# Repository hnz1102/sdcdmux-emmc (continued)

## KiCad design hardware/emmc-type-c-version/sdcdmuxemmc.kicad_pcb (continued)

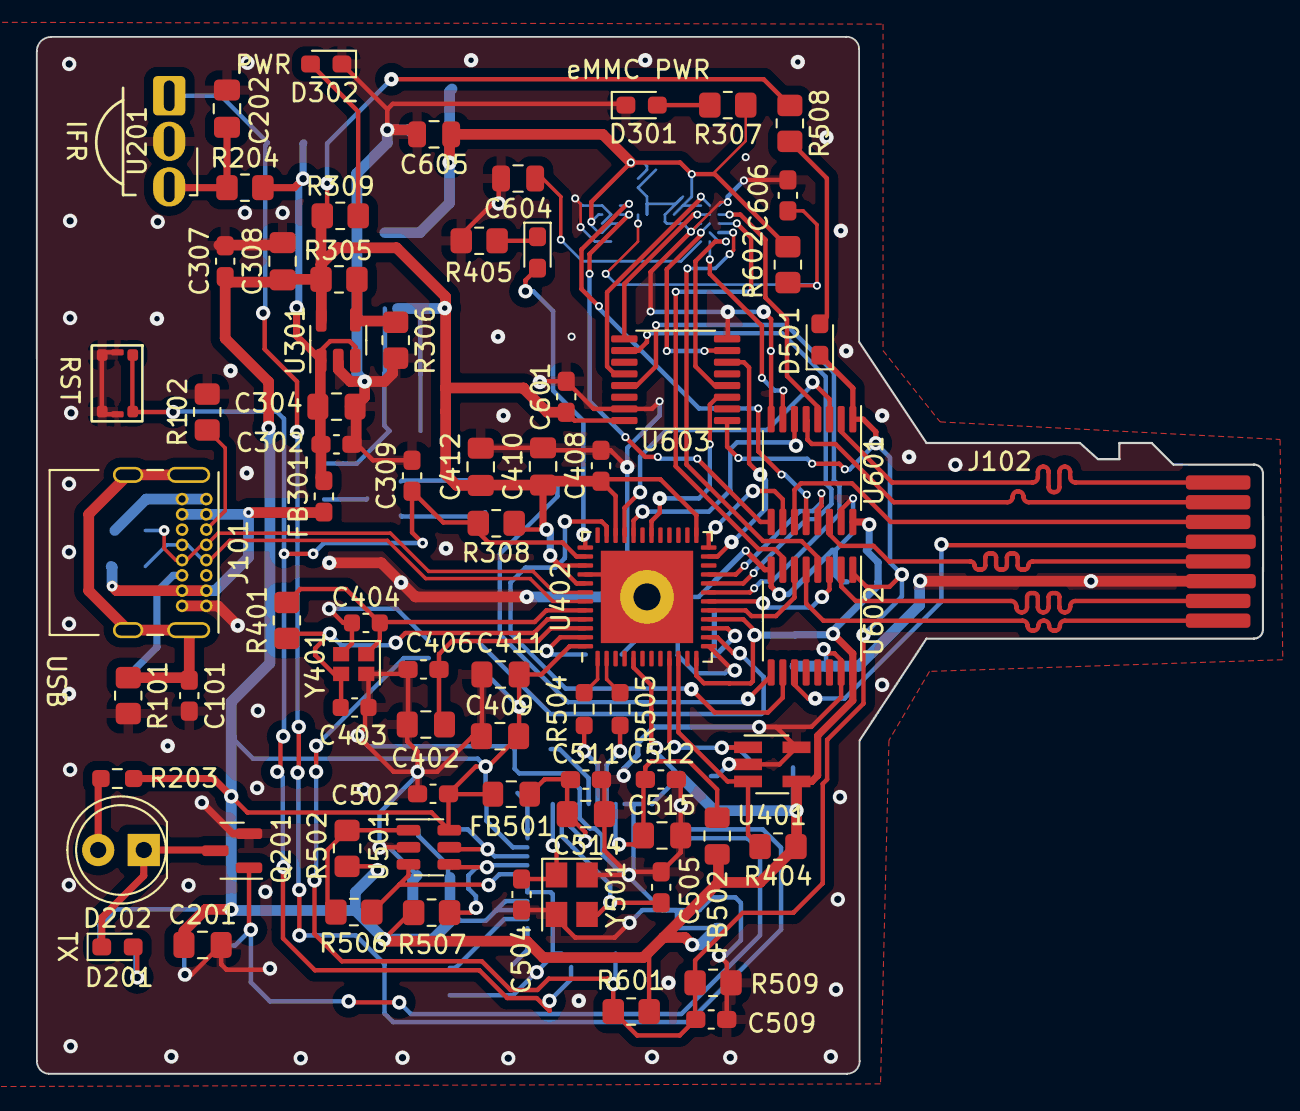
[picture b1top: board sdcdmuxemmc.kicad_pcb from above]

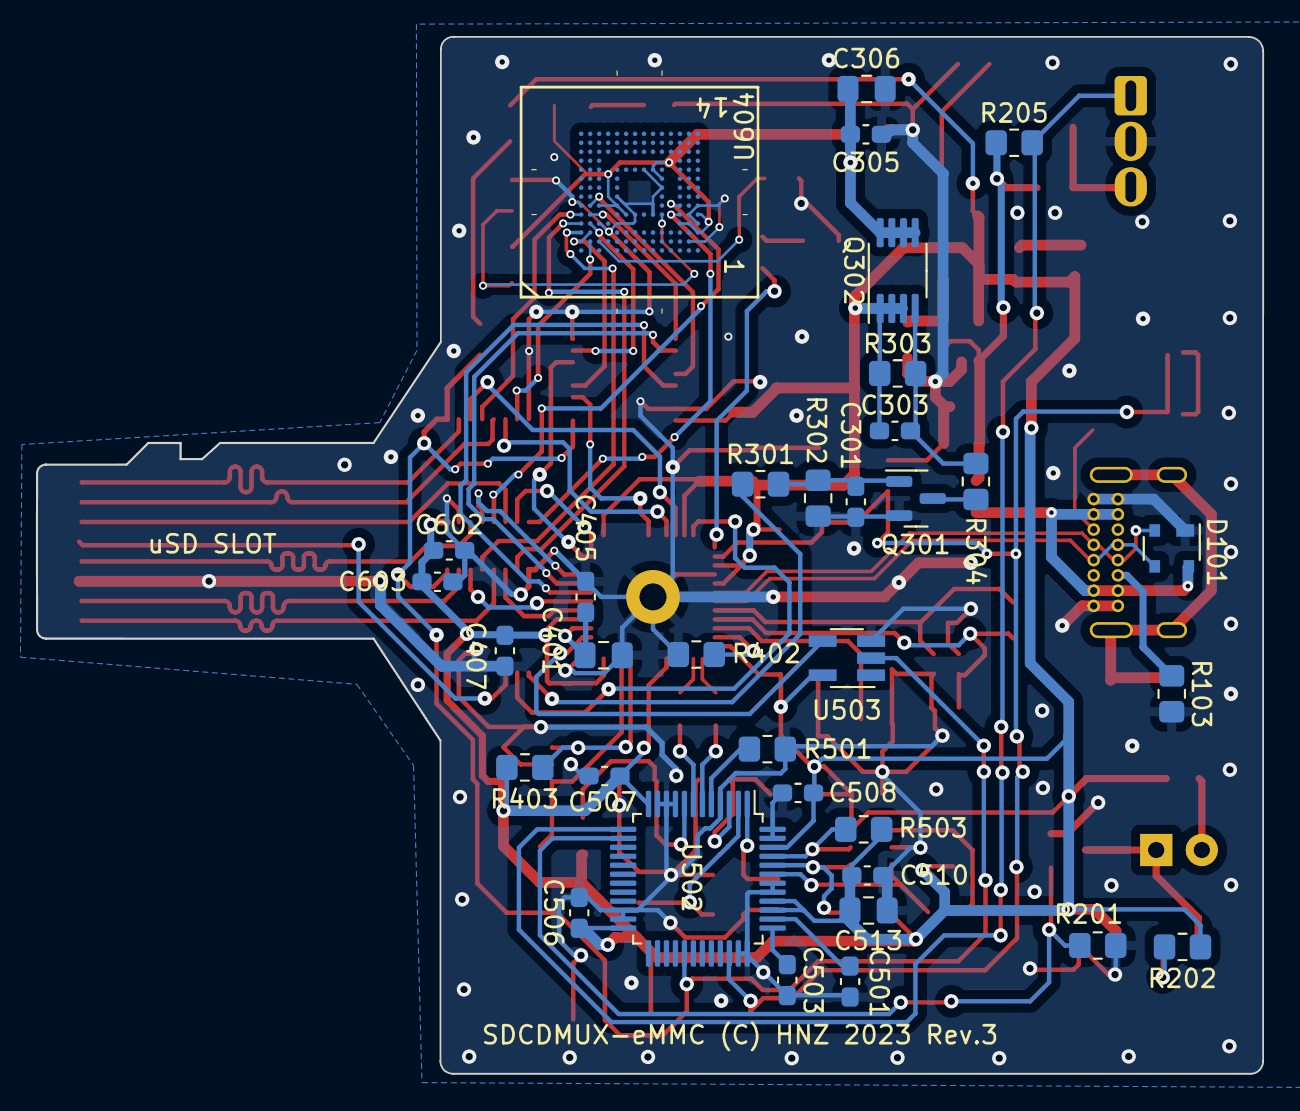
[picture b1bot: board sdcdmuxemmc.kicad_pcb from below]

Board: 2 copper layers, 68.3 x 57.8 mm, 107 parts (34 on the bottom side), 81 nets.

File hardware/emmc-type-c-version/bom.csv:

"Reference","Value","Footprint","digikey","storeURL","Qty"
"C101, C301, C302, C305, C307, C309, C405-C408, C501-C503, C506-C512, C601-C603, C606","0.1uF","Capacitor_SMD:C_0603_1608Metric_Pad1.08x0.95mm_HandSolder","311-1824-1-ND","https://www.digikey.com/en/products/detail/yageo/CC0603MRX7R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","24"
"C201, C304, C306, C308","10uF","Capacitor_SMD:C_0805_2012Metric_Pad1.18x1.45mm_HandSolder","311-3494-1-ND","https://www.digikey.com/en/products/detail/yageo/CC0603MRX5R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","4"
"C202","22uF","Capacitor_SMD:C_0805_2012Metric_Pad1.18x1.45mm_HandSolder","311-3494-1-ND","https://www.digikey.com/en/products/detail/yageo/CC0603MRX5R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","1"
"C303","2.2uF","Capacitor_SMD:C_0603_1608Metric_Pad1.08x0.95mm_HandSolder","311-1795-1-ND","https://www.digikey.com/en/products/detail/yageo/CC0603KRX7R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","1"
"C401, C402, C409, C410","1uF","tbctl:C_0805_2012Metric_Pad1.18x1.45mm_HandSolder","13-CC0603KPX7R7BB105CT-ND","https://www.digikey.com/en/products/detail/yageo/CC0603KPX7R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","4"
"C403, C404","27pF","Capacitor_SMD:C_0603_1608Metric","311-1063-1-ND","https://www.digikey.com/en/products/detail/yageo/CC0603JRNPO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","2"
"C411, C412","4.7uF","tbctl:C_0805_2012Metric_Pad1.18x1.45mm_HandSolder","311-1455-1-ND","https://www.digikey.com/en/products/detail/yageo/CC0603KRX5R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","2"
"C504, C505","27pF","Capacitor_SMD:C_0603_1608Metric_Pad1.08x0.95mm_HandSolder","311-1063-1-ND","https://www.digikey.com/en/products/detail/yageo/CC0603JRNPO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","2"
"C513-C515","4.7uF","Capacitor_SMD:C_0805_2012Metric_Pad1.18x1.45mm_HandSolder","311-1455-1-ND","https://www.digikey.com/en/products/detail/yageo/CC0603KRX5R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","3"
"C604, C605","1uF","Capacitor_SMD:C_0805_2012Metric","13-CC0603KPX7R7BB105CT-ND","https://www.digikey.com/en/products/detail/yageo/CC0603KPX7R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","2"
"D101","PRTR5V0U2X","Package_TO_SOT_SMD:SOT-143","1727-3884-1-ND","https://www.digikey.com/en/products/detail/nexperia-usa-inc/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","1"
"D201, D302, D401","LED RED","tbctl:LED_0603_1608Metric_Pad1.05x0.95mm_HandSolder","511-1587-1-ND","https://www.digikey.com/en/products/detail/rohm-semiconducto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","3"
"D202","OED-EL-1L2","LED_THT:LED_D5.0mm","67-1001-ND","https://www.digikey.com/en/products/detail/lumex-opto-compon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","1"
"D301","eMMC PWR LED RED","tbctl:LED_0603_1608Metric_Pad1.05x0.95mm_HandSolder","511-1587-1-ND","https://www.digikey.com/en/products/detail/rohm-semiconducto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","1"
"D501","TGT SEL LED BLUE","tbctl:LED_0603_1608Metric_Pad1.05x0.95mm_HandSolder","846-1177-1-ND","https://www.digikey.com/en/products/detail/rohm-semiconducto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","1"
"FB301","BK2125HS601-T","tbctl:L_0603_1608Metric_Pad1.05x0.95mm_HandSolder","240-2399-1-ND ","https://www.digikey.com/en/products/detail/laird-signal-inte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","1"
"FB501, FB502","BK2125HS601-T","Inductor_SMD:L_0805_2012Metric_Pad1.15x1.40mm_HandSolder","240-2399-1-ND ","https://www.digikey.com/en/products/detail/laird-signal-inte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","2"
"J101","USB_C_Receptacle_USB2.0_GCT4085","Connector_USB:USB_C_Receptacle_GCT_USB4085","2073-USB4085-GF-ACT-ND","https://www.digikey.com/en/products/detail/gct/USB4085-GF-A/9859662","1"
"J102","uSD-CARD-PAD","tbctl:uSD Card Pad","","","1"
"Q201, Q301","2N7002K","Package_TO_SOT_SMD:SOT-23","2N7002K-7DICT-ND","https://www.digikey.com/en/products/detail/diodes-incorporat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","2"
"Q302","IRF7606TRPBF","Package_SO:MSOP-8_3x3mm_P0.65mm","IRF7606TRPBFCT-ND","https://www.digikey.com/en/products/detail/infineon-technolo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","1"
"R101, R201, R205, R302, R303, R308, R403, R404, R502, R503, R507, R509, R601, R602","10K","tbctl:R_0805_2012Metric_Pad1.20x1.40mm_HandSolder","13-RC0603JR-1010KLCT-ND","https://www.digikey.com/en/products/detail/yageo/RC0603JR-10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","14"
"R102, R103","5.1K","tbctl:R_0805_2012Metric_Pad1.20x1.40mm_HandSolder","13-RC0603JR-1010KLCT-ND","https://www.digikey.com/en/products/detail/yageo/RC0603JR-10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","2"
"R202, R304, R307, R309, R508","1K","tbctl:R_0805_2012Metric_Pad1.20x1.40mm_HandSolder","13-RC0603JR-101KLCT-ND","https://www.digikey.com/en/products/detail/yageo/RC0603JR-10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","5"
"R203","33R","Resistor_SMD:R_0603_1608Metric_Pad0.98x0.95mm_HandSolder","311-33GRCT-ND","https://www.digikey.com/en/products/detail/yageo/RC0603JR-07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","1"
"R204","100","tbctl:R_0805_2012Metric_Pad1.20x1.40mm_HandSolder","13-RC0603JR-1010KLCT-ND","https://www.digikey.com/en/products/detail/yageo/RC0603JR-10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","1"
"R301, R506","2K","tbctl:R_0805_2012Metric_Pad1.20x1.40mm_HandSolder","311-2.0KGRCT-ND","https://www.digikey.com/en/products/detail/yageo/RC0603JR-07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","2"
"R305","20K 1%","tbctl:R_0805_2012Metric_Pad1.20x1.40mm_HandSolder","13-RC0603FR-1320KLCT-ND","https://www.digikey.com/en/products/detail/yageo/RC0603FR-13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","1"
"R306, R402, R501","12K 1%","tbctl:R_0805_2012Metric_Pad1.20x1.40mm_HandSolder","311-12.0KHRCT-ND","https://www.digikey.com/en/products/detail/yageo/RC0603FR-07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","3"
"R401","1M","tbctl:R_0805_2012Metric_Pad1.20x1.40mm_HandSolder","311-1.0MGRCT-ND","https://www.digikey.com/en/products/detail/yageo/RC0603JR-07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","1"
"R405","330R","tbctl:R_0805_2012Metric_Pad1.20x1.40mm_HandSolder","311-330GRCT-ND","https://www.digikey.com/en/products/detail/yageo/RC0603JR-07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","1"
"R504, R505","27R","Resistor_SMD:R_0603_1608Metric_Pad0.98x0.95mm_HandSolder","311-27GRCT-ND","https://www.digikey.com/en/products/detail/yageo/RC0603JR-07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","2"
"SW301","RESET SW","tbctl:WS-TASV SMT Tact Switch","732-435151014824CT-ND","https://www.digikey.com/en/products/detail/w%C3%BCrth-elektr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","1"
"U201","TSSP4038","tbctl:TSSP4038","TSSP4038-ND","https://www.digikey.com/en/products/detail/vishay-semiconduc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","1"
"U301","SPX3819M5-L","Package_TO_SOT_SMD:SOT-23-5","1016-1871-1-ND","https://www.digikey.com/en/products/detail/maxlinear-inc/SPX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","1"
"U401","AT24MAC402-STUM","Package_TO_SOT_SMD:SOT-23-5_HandSoldering","AT24MAC402-STUM-TCT-ND ","https://www.digikey.com/en/products/detail/microchip-technol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","1"
"U402","USB2640-HZH-02","tbctl:QFN-48-1EP_7x7mm_P0.5mm_EP5.15x5.15mm","USB2640-HZH-02-ND","https://www.digikey.com/en/products/detail/microchip-technol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","1"
"U501","93LCxxBxxOT","Package_TO_SOT_SMD:SOT-23-6","93LC56BT-I/OTCT-ND","https://www.digikey.com/en/products/detail/microchip-technol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","1"
"U502","FT232HL","Package_QFP:LQFP-48_7x7mm_P0.5mm","768-1348-ND","https://www.digikey.com/en/products/detail/ftdi-future-techn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","1"
"U503","74AHC1G14","Package_TO_SOT_SMD:SOT-23-5_HandSoldering","74AHC1G14W5-7DICT-ND","https://www.digikey.com/en/products/detail/diodes-incorporat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","1"
"U601-U603","TMUX1574PWR","Package_SO:TSSOP-16_4.4x5mm_P0.65mm","296-53444-1-ND ","https://www.digikey.com/en/products/detail/texas-instruments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","3"
"U604","EM32VSUKN","tbctl:EM32VSUKN FPGA153","3247-EM32VSUKN-BA000-2-ND","https://www.digikey.com/en/products/detail/delkin-devices-in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","1"
"Y401","24MHz","tbctl:Crystal_SMD_2016-4Pin_2.0x1.6mm","XC3064CT-ND","https://www.digikey.com/en/products/detail/ecs-inc/ECS-240-1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","1"
"Y501","12MHz","Crystal:Crystal_SMD_3225-4Pin_3.2x2.5mm","SER3682CT-ND","https://www.digikey.com/en/products/detail/epson/FA-238V-12-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","1"

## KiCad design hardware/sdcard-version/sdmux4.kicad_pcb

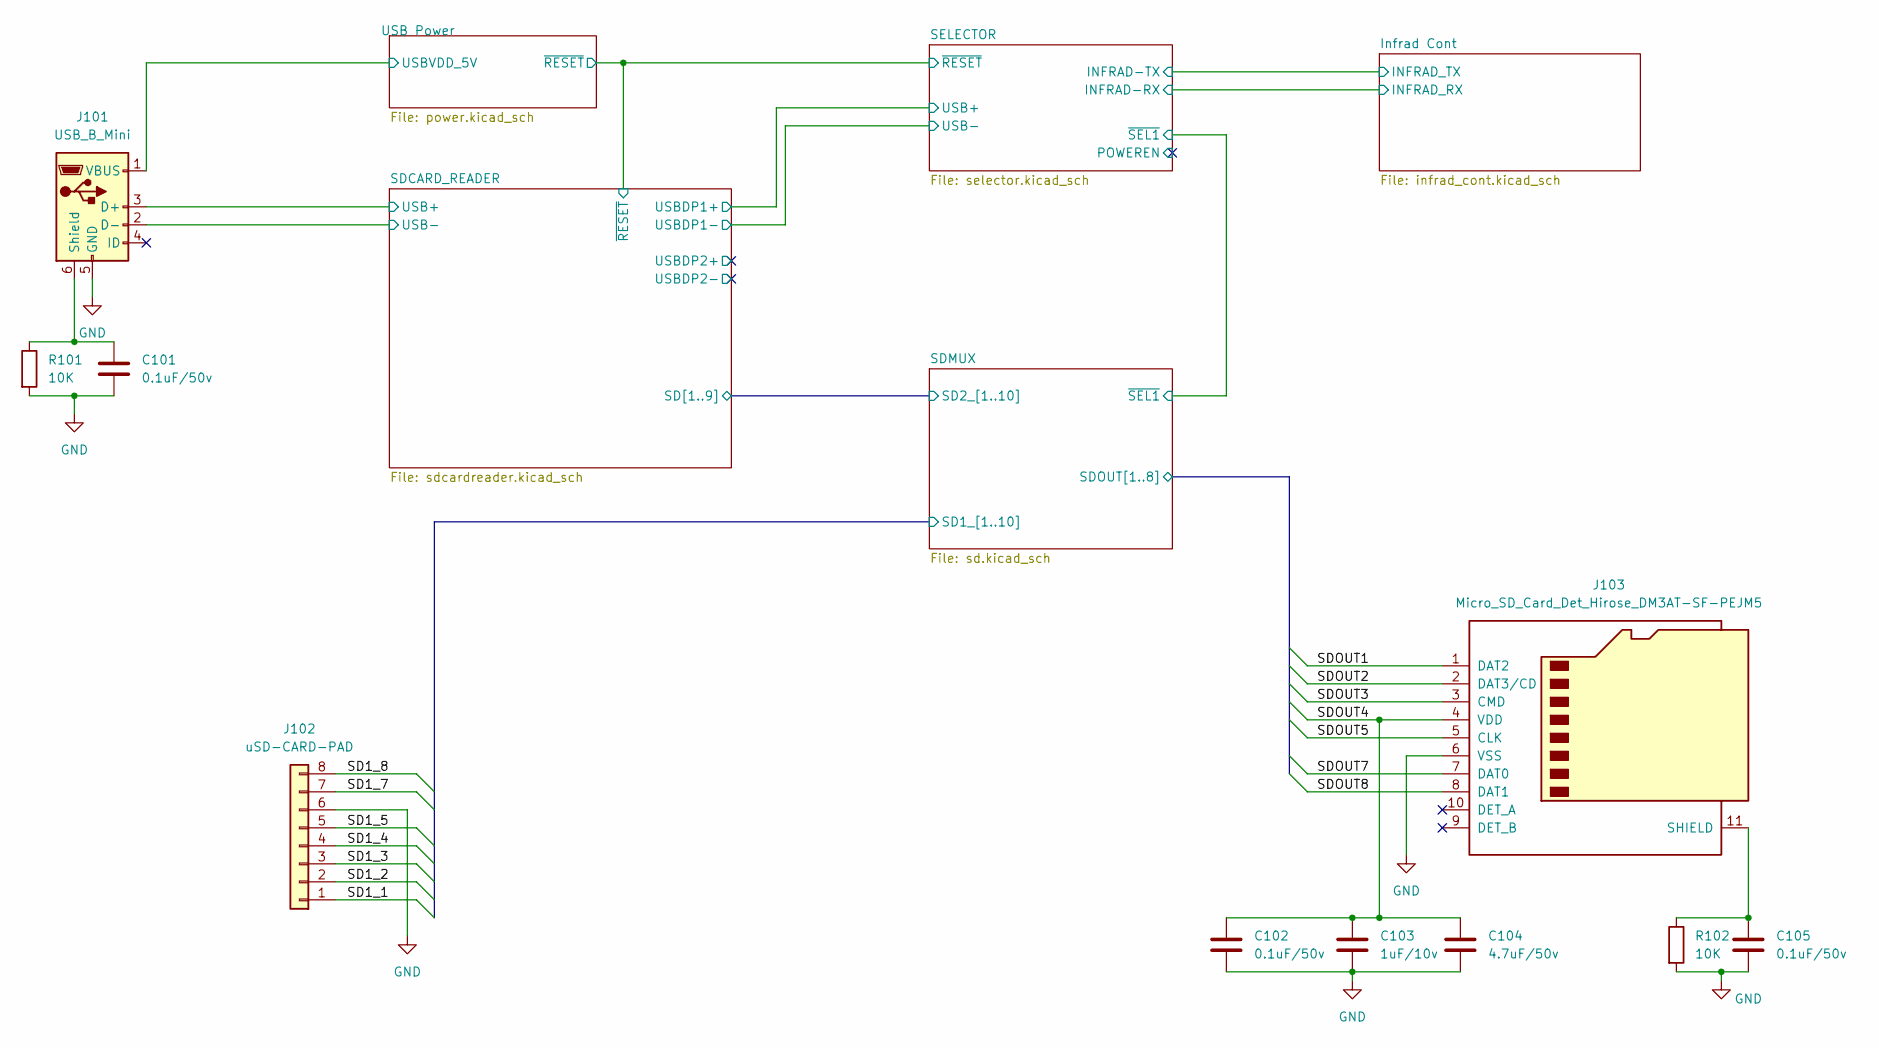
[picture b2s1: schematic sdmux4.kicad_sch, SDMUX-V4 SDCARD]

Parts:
C101, C102, C105: 0.1uF/50v; C_0603_1608Metric_Pad1.08x0.95mm_HandSolder
C103: 1uF/10v; C_0805_2012Metric_Pad1.18x1.45mm_HandSolder
C104: 4.7uF/50v; C_0805_2012Metric_Pad1.18x1.45mm_HandSolder
J101: USB_B_Mini; usb mini B connector c2235 dim 2
J102: uSD-CARD-PAD; uSD Card Pad
J103: Micro_SD_Card_Det_Hirose_DM3AT-SF-PEJM5; microSD_HC_Hirose_DM3AT-SF-PEJM5
R101, R102: 10K; R_0805_2012Metric_Pad1.20x1.40mm_HandSolder

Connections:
/SDCARD_READER/USB+: J101.3 (D+); also elsewhere on the board
/SDCARD_READER/USB-: J101.2 (D-); also elsewhere on the board
/SDMUX/SD1_1: J102.1; also elsewhere on the board
/SDMUX/SD1_2: J102.2; also elsewhere on the board
/SDMUX/SD1_3: J102.3; also elsewhere on the board
/SDMUX/SD1_4: J102.4; also elsewhere on the board
/SDMUX/SD1_5: J102.5; also elsewhere on the board
/SDMUX/SD1_7: J102.7; also elsewhere on the board
/SDMUX/SD1_8: J102.8; also elsewhere on the board
/SDMUX/SDOUT1: J103.1 (DAT2); also elsewhere on the board
/SDMUX/SDOUT2: J103.2 (DAT3/CD); also elsewhere on the board
/SDMUX/SDOUT3: J103.3 (CMD); also elsewhere on the board
/SDMUX/SDOUT4: C102.1, C103.1, C104.1, J103.4 (VDD); also elsewhere on the board
/SDMUX/SDOUT5: J103.5 (CLK); also elsewhere on the board
/SDMUX/SDOUT7: J103.7 (DAT0); also elsewhere on the board
/SDMUX/SDOUT8: J103.8 (DAT1); also elsewhere on the board
/USB Power/USBVDD_5V: J101.1 (VBUS); also elsewhere on the board
GND: C101.2, C102.2, C103.2, C104.2, C105.2, J101.5 (GND), J102.6, J103.6 (VSS), R101.2, R102.2; also elsewhere on the board
unnamed: C101.1, J101.6 (Shield), R101.1
unnamed: C105.1, J103.11 (SHIELD), R102.1

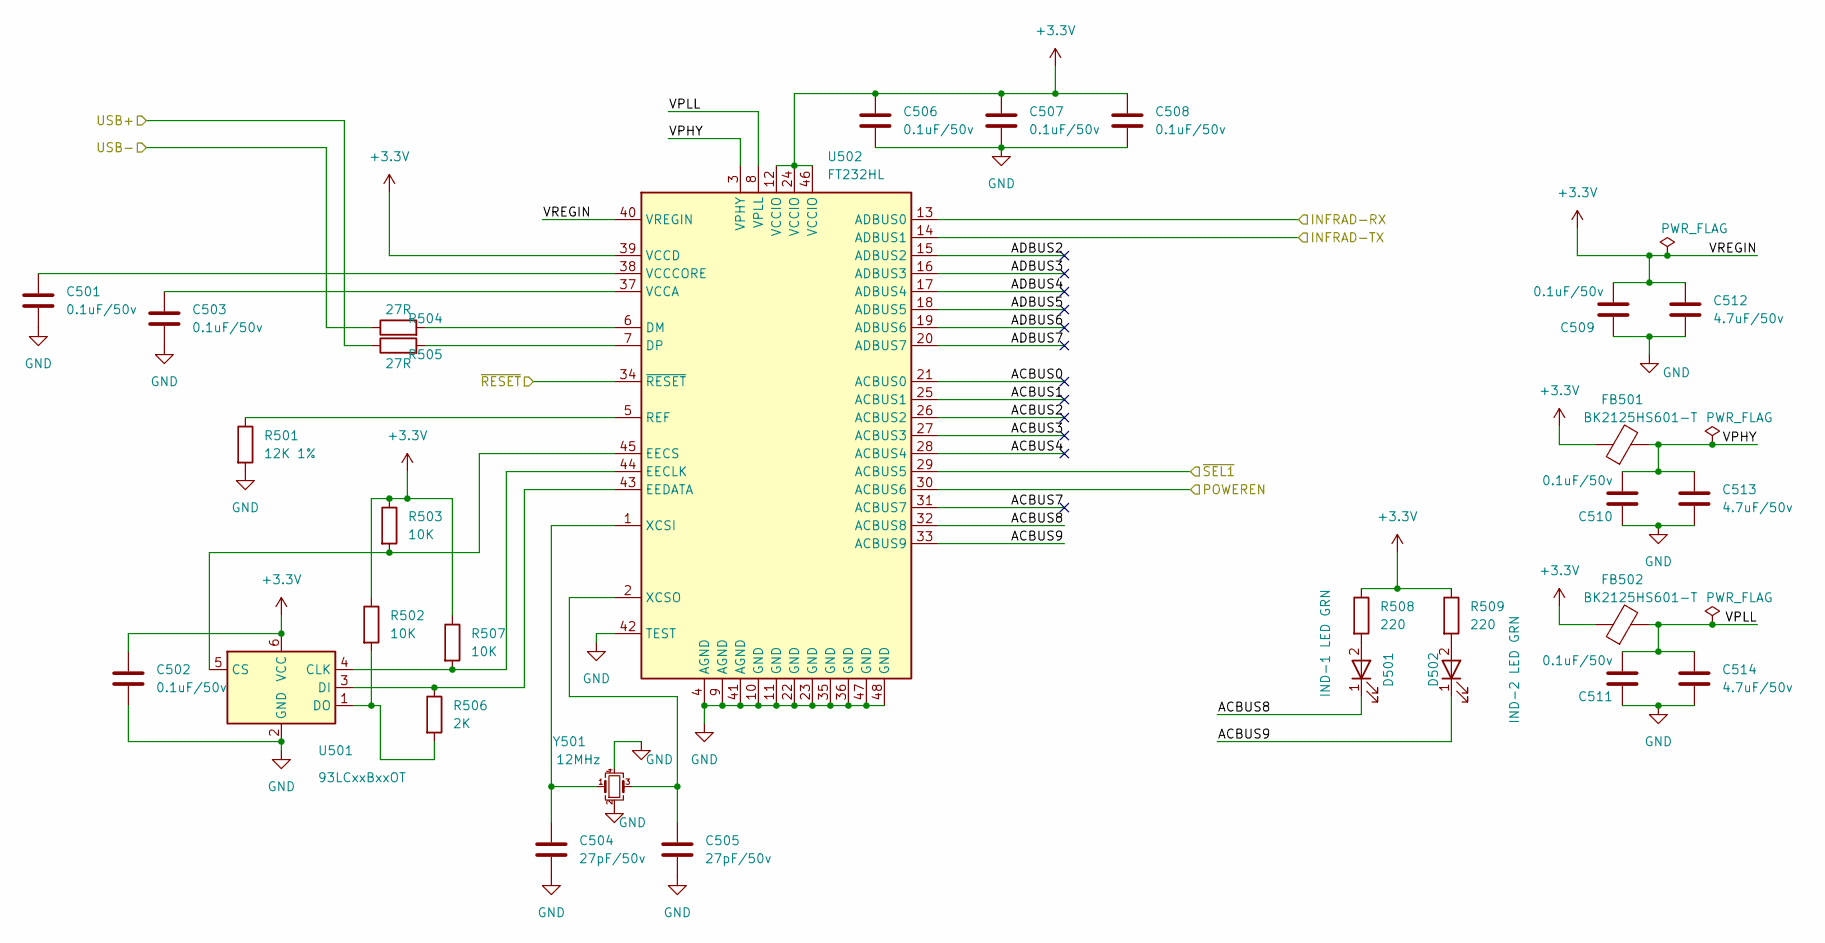
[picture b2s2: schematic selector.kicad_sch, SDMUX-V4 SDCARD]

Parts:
C501, C502, C503, C506, C507, C508, C509, C510, C511: 0.1uF/50v; C_0603_1608Metric_Pad1.08x0.95mm_HandSolder
C504, C505: 27pF/50v; C_0603_1608Metric_Pad1.08x0.95mm_HandSolder
C512, C513, C514: 4.7uF/50v; C_0805_2012Metric_Pad1.18x1.45mm_HandSolder
D501: IND-1 LED GRN; LED_0603_1608Metric_Pad1.05x0.95mm_HandSolder
D502: IND-2 LED GRN; LED_0603_1608Metric_Pad1.05x0.95mm_HandSolder
FB501, FB502: BK2125HS601-T; L_0805_2012Metric_Pad1.15x1.40mm_HandSolder
R501: 12K 1%; R_0805_2012Metric_Pad1.20x1.40mm_HandSolder
R502, R503, R507: 10K; R_0805_2012Metric_Pad1.20x1.40mm_HandSolder
R504, R505: 27R; R_0603_1608Metric_Pad0.98x0.95mm_HandSolder
R506: 2K; R_0805_2012Metric_Pad1.20x1.40mm_HandSolder
R508, R509: 220; R_0805_2012Metric_Pad1.20x1.40mm_HandSolder
U501: 93LCxxBxxOT; SOT-23-6
U502: FT232HL; LQFP-48_7x7mm_P0.5mm
Y501: 12MHz; Crystal_SMD_3225-4Pin_3.2x2.5mm

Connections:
+3.3V: C502.1, C506.1, C507.1, C508.1, C509.1, C512.1, FB501.1, FB502.1, R502.1, R503.1, R507.1, R508.1, R509.1, U501.6 (VCC), U502.12 (VCCIO), U502.24 (VCCIO), U502.39 (VCCD), U502.40 (VREGIN), U502.46 (VCCIO); also elsewhere on the board
/Infrad Cont/INFRAD_RX: U502.13 (ADBUS0); also elsewhere on the board
/Infrad Cont/INFRAD_TX: U502.14 (ADBUS1); also elsewhere on the board
/SDCARD_READER/USBDP1+: R505.1; also elsewhere on the board
/SDCARD_READER/USBDP1-: R504.1; also elsewhere on the board
/SDCARD_READER/~RESET: U502.34 (~RESET); also elsewhere on the board
/SDMUX/~SEL1: U502.29 (ACBUS5); also elsewhere on the board
/SELECTOR/ACBUS0: U502.21 (ACBUS0)
/SELECTOR/ACBUS1: U502.25 (ACBUS1)
/SELECTOR/ACBUS2: U502.26 (ACBUS2)
/SELECTOR/ACBUS3: U502.27 (ACBUS3)
/SELECTOR/ACBUS4: U502.28 (ACBUS4)
/SELECTOR/ACBUS7: U502.31 (ACBUS7)
/SELECTOR/ACBUS8: D501.1 (K), U502.32 (ACBUS8)
/SELECTOR/ACBUS9: D502.1 (K), U502.33 (ACBUS9)
/SELECTOR/ADBUS2: U502.15 (ADBUS2)
/SELECTOR/ADBUS3: U502.16 (ADBUS3)
/SELECTOR/ADBUS4: U502.17 (ADBUS4)
/SELECTOR/ADBUS5: U502.18 (ADBUS5)
/SELECTOR/ADBUS6: U502.19 (ADBUS6)
/SELECTOR/ADBUS7: U502.20 (ADBUS7)
/SELECTOR/POWEREN: U502.30 (ACBUS6)
/SELECTOR/VPHY: C510.1, C513.1, FB501.2, U502.3 (VPHY)
/SELECTOR/VPLL: C511.1, C514.1, FB502.2, U502.8 (VPLL)
GND: C501.2, C502.2, C503.2, C504.2, C505.2, C506.2, C507.2, C508.2, C509.2, C510.2, C511.2, C512.2, C513.2, C514.2, R501.2, U501.2 (GND), U502.4 (AGND), U502.9 (AGND), U502.10 (GND), U502.11 (GND), U502.22 (GND), U502.23 (GND), U502.35 (GND), U502.36 (GND), U502.41 (AGND), U502.42 (TEST), U502.47 (GND), U502.48 (GND), Y501.2, Y501.4; also elsewhere on the board
unnamed: D501.2 (A), R508.2
unnamed: D502.2 (A), R509.2
unnamed: R507.2, U501.4 (CLK), U502.44 (EECLK)
unnamed: R503.2, U501.5 (CS), U502.45 (EECS)
unnamed: R506.1, U501.3 (DI), U502.43 (EEDATA)
unnamed: R502.2, R506.2, U501.1 (DO)
unnamed: R504.2, U502.6 (DM)
unnamed: R505.2, U502.7 (DP)
unnamed: R501.1, U502.5 (REF)
unnamed: C503.1, U502.37 (VCCA)
unnamed: C501.1, U502.38 (VCCCORE)
unnamed: C504.1, U502.1 (XCSI), Y501.1
unnamed: C505.1, U502.2 (XCSO), Y501.3

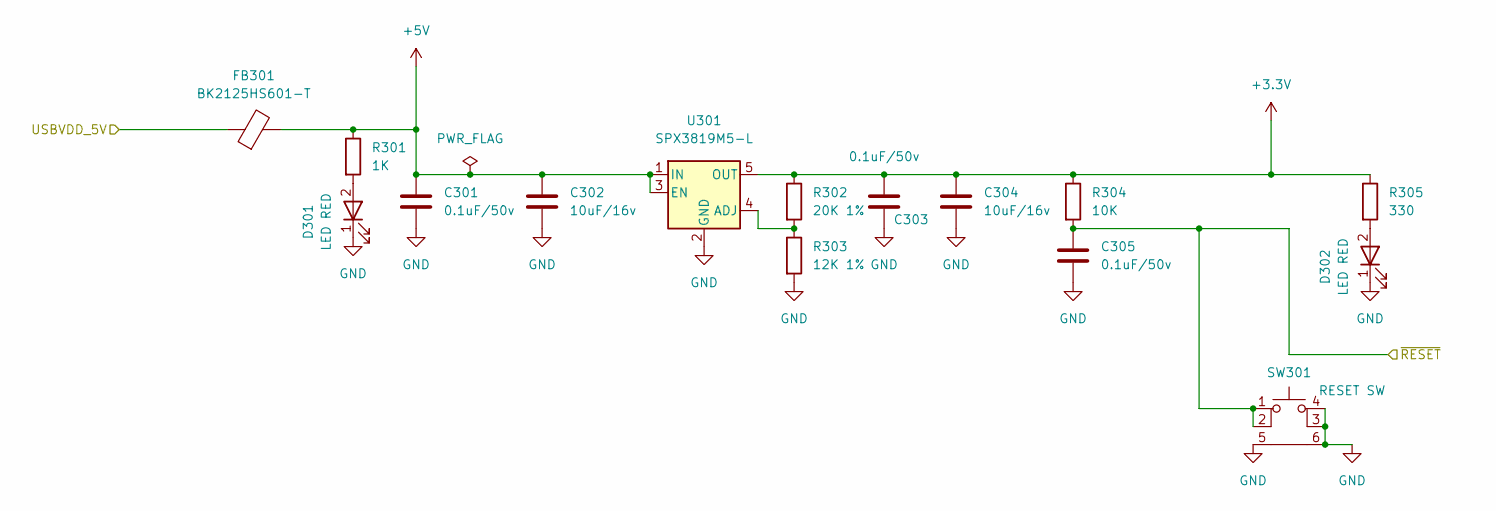
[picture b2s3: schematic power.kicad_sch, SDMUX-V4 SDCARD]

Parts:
C301, C303, C305: 0.1uF/50v; C_0603_1608Metric_Pad1.08x0.95mm_HandSolder
C302, C304: 10uF/16v; C_0805_2012Metric_Pad1.18x1.45mm_HandSolder
D301, D302: LED RED; LED_0603_1608Metric_Pad1.05x0.95mm_HandSolder
FB301: BK2125HS601-T; L_0603_1608Metric_Pad1.05x0.95mm_HandSolder
R301: 1K; R_0805_2012Metric_Pad1.20x1.40mm_HandSolder
R302: 20K 1%; R_0805_2012Metric_Pad1.20x1.40mm_HandSolder
R303: 12K 1%; R_0805_2012Metric_Pad1.20x1.40mm_HandSolder
R304: 10K; R_0805_2012Metric_Pad1.20x1.40mm_HandSolder
R305: 330; R_0805_2012Metric_Pad1.20x1.40mm_HandSolder
SW301: RESET SW; WS-TASV SMT Tact Switch
U301: SPX3819M5-L; SOT-23-5

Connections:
+3.3V: C303.1, C304.1, R302.1, R304.1, R305.1, U301.5 (OUT); also elsewhere on the board
+5V: C301.1, C302.1, FB301.2, R301.1, U301.1 (IN), U301.3 (EN); also elsewhere on the board
/SDCARD_READER/~RESET: C305.1, R304.2, SW301.1, SW301.2; also elsewhere on the board
/USB Power/USBVDD_5V: FB301.1; also elsewhere on the board
GND: C301.2, C302.2, C303.2, C304.2, C305.2, D301.1 (K), D302.1 (K), R303.2, SW301.3 (K), SW301.4 (A), SW301.5, SW301.6, U301.2 (GND); also elsewhere on the board
unnamed: D301.2 (A), R301.2
unnamed: D302.2 (A), R305.2
unnamed: R302.2, R303.1, U301.4 (ADJ)

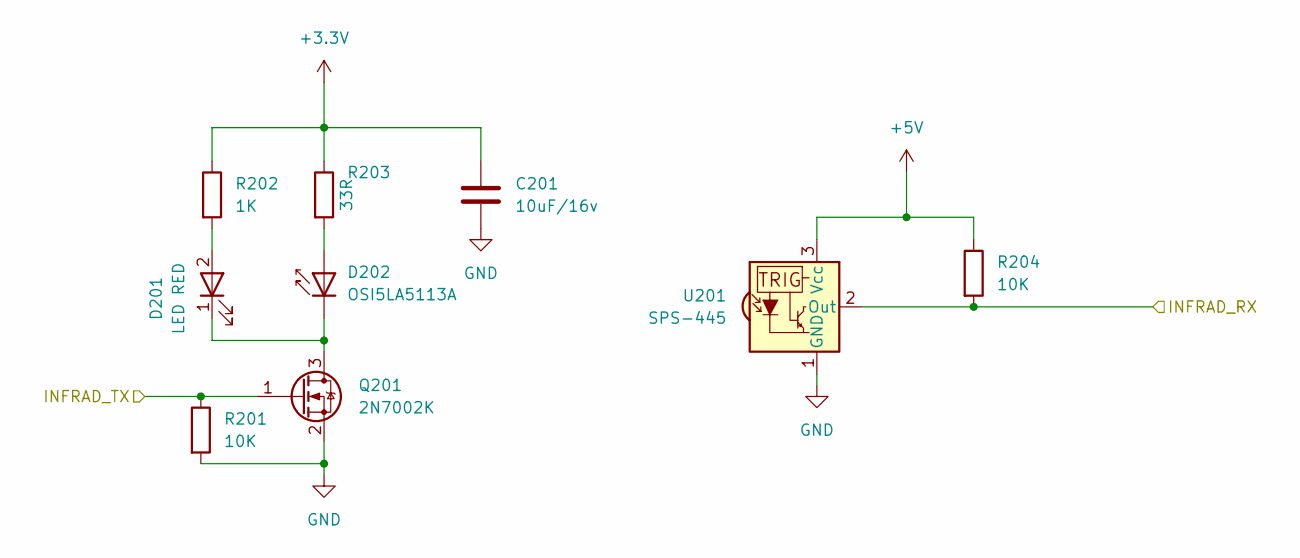
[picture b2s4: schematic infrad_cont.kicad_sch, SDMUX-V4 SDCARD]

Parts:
C201: 10uF/16v; C_0805_2012Metric_Pad1.18x1.45mm_HandSolder
D201: LED RED; LED_0603_1608Metric_Pad1.05x0.95mm_HandSolder
D202: OSI5LA5113A; LED_D5.0mm
Q201: 2N7002K; SOT-23
R201, R204: 10K; R_0805_2012Metric_Pad1.20x1.40mm_HandSolder
R202: 1K; R_0805_2012Metric_Pad1.20x1.40mm_HandSolder
R203: 33R; R_0603_1608Metric_Pad0.98x0.95mm_HandSolder
U201: SPS-445; SPS445 3pin

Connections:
+3.3V: C201.1, R202.1, R203.1; also elsewhere on the board
+5V: R204.1, U201.3 (Vcc); also elsewhere on the board
/Infrad Cont/INFRAD_RX: R204.2, U201.2 (Out); also elsewhere on the board
/Infrad Cont/INFRAD_TX: Q201.1 (G), R201.1; also elsewhere on the board
GND: C201.2, Q201.2 (S), R201.2, U201.1 (GND); also elsewhere on the board
unnamed: D201.2 (A), R202.2
unnamed: D201.1 (K), D202.1 (K), Q201.3 (D)
unnamed: D202.2 (A), R203.2

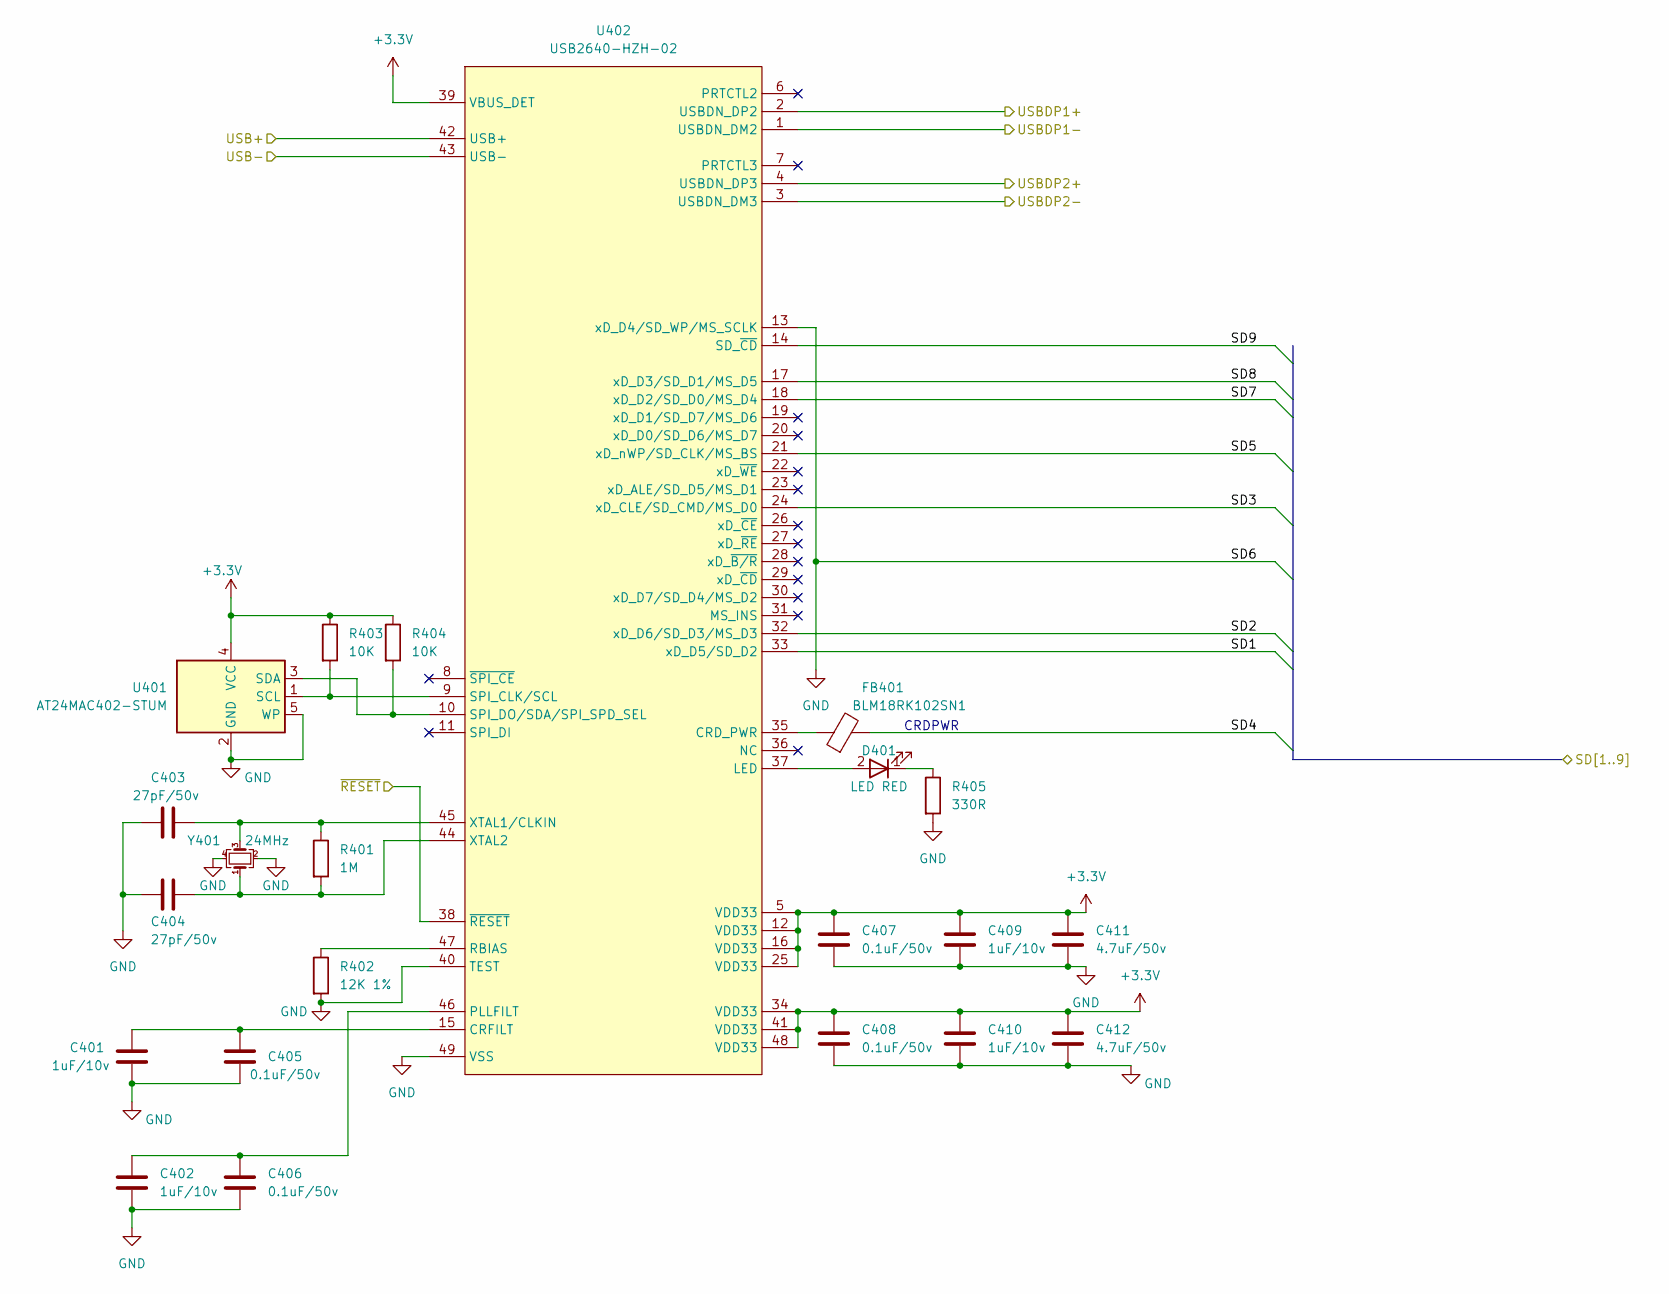
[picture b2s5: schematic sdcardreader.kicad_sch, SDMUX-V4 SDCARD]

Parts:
C401, C402, C409, C410: 1uF/10v; C_0805_2012Metric_Pad1.18x1.45mm_HandSolder
C403, C404: 27pF/50v; C_0603_1608Metric
C405, C406, C407, C408: 0.1uF/50v; C_0603_1608Metric_Pad1.08x0.95mm_HandSolder
C411, C412: 4.7uF/50v; C_0805_2012Metric_Pad1.18x1.45mm_HandSolder
D401: LED RED; LED_0603_1608Metric_Pad1.05x0.95mm_HandSolder
FB401: BLM18RK102SN1; L_0603_1608Metric_Pad1.05x0.95mm_HandSolder
R401: 1M; R_0805_2012Metric_Pad1.20x1.40mm_HandSolder
R402: 12K 1%; R_0805_2012Metric_Pad1.20x1.40mm_HandSolder
R403, R404: 10K; R_0805_2012Metric_Pad1.20x1.40mm_HandSolder
R405: 330R; R_0805_2012Metric_Pad1.20x1.40mm_HandSolder
U401: AT24MAC402-STUM; SOT-23-5_HandSoldering
U402: USB2640-HZH-02; QFN-48-1EP_7x7mm_P0.5mm_EP5.15x5.15mm
Y401: 24MHz; Crystal_SMD_2016-4Pin_2.0x1.6mm

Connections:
+3.3V: C407.1, C408.1, C409.1, C410.1, C411.1, C412.1, R403.1, R404.1, U401.4 (VCC), U402.5 (VDD33), U402.12 (VDD33), U402.16 (VDD33), U402.25 (VDD33), U402.34 (VDD33), U402.39 (VBUS_DET), U402.41 (VDD33), U402.48 (VDD33); also elsewhere on the board
/SDCARD_READER/SD1: U402.33 (xD_D5/SD_D2); also elsewhere on the board
/SDCARD_READER/SD2: U402.32 (xD_D6/SD_D3/MS_D3); also elsewhere on the board
/SDCARD_READER/SD3: U402.24 (xD_CLE/SD_CMD/MS_D0); also elsewhere on the board
/SDCARD_READER/SD4: FB401.2; also elsewhere on the board
/SDCARD_READER/SD5: U402.21 (xD_nWP/SD_CLK/MS_BS); also elsewhere on the board
/SDCARD_READER/SD7: U402.18 (xD_D2/SD_D0/MS_D4); also elsewhere on the board
/SDCARD_READER/SD8: U402.17 (xD_D3/SD_D1/MS_D5); also elsewhere on the board
/SDCARD_READER/SD9: U402.14 (SD_~CD); also elsewhere on the board
/SDCARD_READER/USB+: U402.42 (USB+); also elsewhere on the board
/SDCARD_READER/USB-: U402.43 (USB-); also elsewhere on the board
/SDCARD_READER/USBDP1+: U402.2 (USBDN_DP2); also elsewhere on the board
/SDCARD_READER/USBDP1-: U402.1 (USBDN_DM2); also elsewhere on the board
/SDCARD_READER/USBDP2+: U402.4 (USBDN_DP3)
/SDCARD_READER/USBDP2-: U402.3 (USBDN_DM3)
/SDCARD_READER/~RESET: U402.38 (~RESET); also elsewhere on the board
GND: C401.2, C402.2, C403.1, C404.1, C405.2, C406.2, C407.2, C408.2, C409.2, C410.2, C411.2, C412.2, R402.2, R405.2, U401.2 (GND), U401.5 (WP), U402.13 (xD_D4/SD_WP/MS_SCLK), U402.40 (TEST), U402.49 (VSS), Y401.2, Y401.4; also elsewhere on the board
unnamed: D401.2 (A), U402.37 (LED)
unnamed: D401.1 (K), R405.1
unnamed: R403.2, U401.1 (SCL), U402.9 (SPI_CLK/SCL)
unnamed: R404.2, U401.3 (SDA), U402.10 (SPI_DO/SDA/SPI_SPD_SEL)
unnamed: FB401.1, U402.35 (CRD_PWR)
unnamed: C401.1, C405.1, U402.15 (CRFILT)
unnamed: C402.1, C406.1, U402.46 (PLLFILT)
unnamed: R402.1, U402.47 (RBIAS)
unnamed: C403.2, R401.1, U402.45 (XTAL1/CLKIN), Y401.3
unnamed: C404.2, R401.2, U402.44 (XTAL2), Y401.1

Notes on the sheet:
CRDPWR
